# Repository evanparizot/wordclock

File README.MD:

# WordClock

This project is not a word clock based on the [wikipedia](https://en.wikipedia.org/wiki/Word_clock) definition, but rather just an aesthetic choice of representing time. Rather than showing something like a clock face or time in 12 hour / 24 hour format, a wordclock spells out the time using words. One of the more well known examples of wordclocks being produced is from the company [QLOCKTWO](https://qlocktwo.com/us?___from_store=de). Unfortunately, at it's retail price of $1,500+, they can be pretty expensive.

This project is to provide files for those who wish to build their own instead. It's been inspired by repositories such as [this](https://github.com/LikeClockwork/LargeWordClock) on providing both the pcb schematics, as well source code for anyone to look at. 

## Project Overview

Included in this repository are the graphics used to make up the clock face, the pcb schematics that outline the circuitry for the clock, as well the source code for the firmware used to run the wordclock. You can find each in their respective repostories. 

The pcb schematics were made using a mixture of Altium Designer and KiCad. The microcontroller is a variant of the STM32, with source code written in Rust. Each sub folder has further details on how to work with each of those components.

## Development Progress

Developmet of this project is ongoing and will be for some time. I will be keeping milestones in a Github project for the repository to track progress.

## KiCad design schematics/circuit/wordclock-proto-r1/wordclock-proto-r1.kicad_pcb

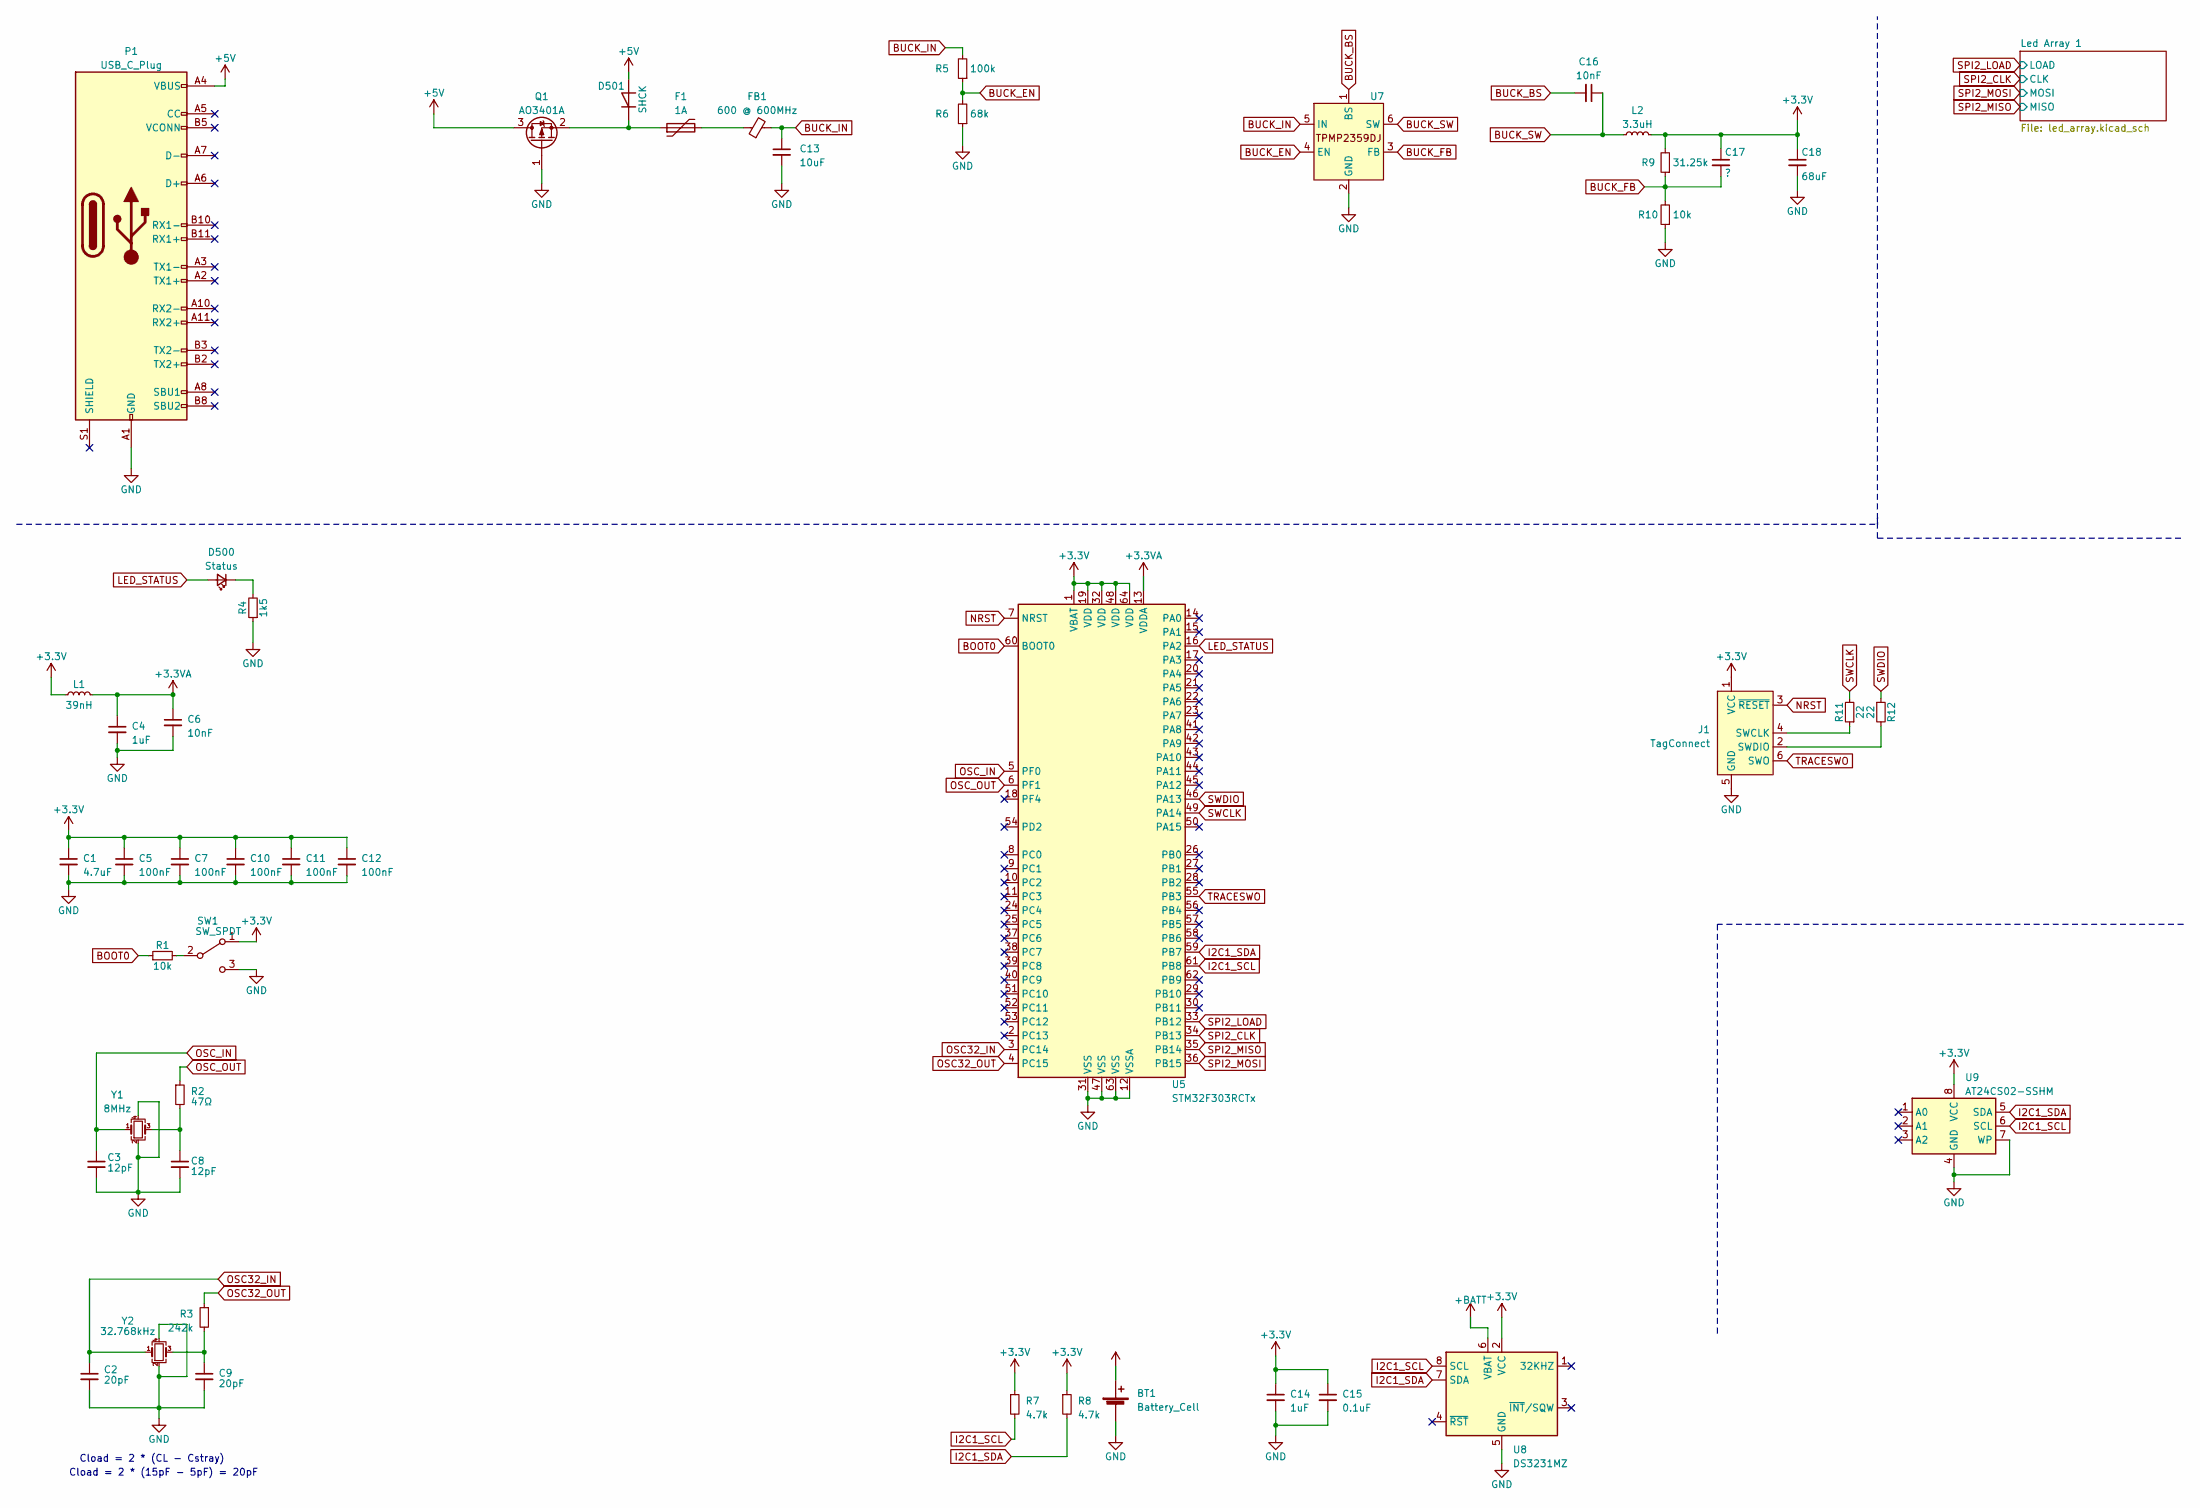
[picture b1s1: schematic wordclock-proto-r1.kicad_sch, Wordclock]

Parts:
BT1: Battery_Cell; BatteryHolder_Keystone_3002_1x2032
C1: 4.7uF; C_0603_1608Metric
C2, C9: 20pF; C_0402_1005Metric
C3, C8: 12pF; C_0402_1005Metric
C4, C14: 1uF; C_0402_1005Metric
C5, C7, C10, C11, C12: 100nF; C_0402_1005Metric
C6: 10nF; C_0402_1005Metric
C13: 10uF; C_0805_2012Metric
C15: 0.1uF; C_0402_1005Metric
C16: 10nF; C_0603_1608Metric
C17: ?; C_0603_1608Metric
C18: 68uF; C_0603_1608Metric
D500: Status; LED_0603_1608Metric
D501: SHCK; D_SOD-123
F1: 1A; Fuse_1206_3216Metric
FB1: 600 @ 600MHz; L_0805_2012Metric
J1: TagConnect; Tag-Connect_TC2030-IDC-FP_2x03_P1.27mm_Vertical
L1: 39nH; L_Sunlord_MWSA0518S
L2: 3.3uH; L_0402_1005Metric
P1: USB_C_Plug; USB_C_Receptacle_GCT_USB4115-03-C
Q1: AO3401A; SOT-23
R1: 10k; R_0603_1608Metric
R2: 47Ω; R_0402_1005Metric
R3: 242k; R_0402_1005Metric
R4: 1k5; R_0402_1005Metric
R5: 100k; R_0805_2012Metric
R6: 68k; R_0805_2012Metric
R7, R8: 4.7k; R_0402_1005Metric
R9: 31.25k; R_0805_2012Metric
R10: 10k; R_0805_2012Metric
R11, R12: 22; R_0603_1608Metric
SW1: SW_SPDT; SW_SPDT_PCM12
U5: STM32F303RCTx; LQFP-64_10x10mm_P0.5mm
U7: SOT-23-6
U8: DS3231MZ; SOIC-8_3.9x4.9mm_P1.27mm
U9: AT24CS02-SSHM; SOIC-8_3.9x4.9mm_P1.27mm
Y1: 8MHz; Crystal_SMD_3225-4Pin_3.2x2.5mm
Y2: 32.768kHz; Crystal_SMD_3225-4Pin_3.2x2.5mm

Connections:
+3.3V: C1.1, C5.1, C7.1, C10.1, C11.1, C12.1, C14.1, C15.1, C17.1, C18.1, J1.1 (VCC), L1.1, L2.2, R7.1, R8.1, R9.2, SW1.1 (A), U5.1 (VBAT), U5.19 (VDD), U5.32 (VDD), U5.48 (VDD), U5.64 (VDD), U8.2 (VCC), U9.8 (VCC); also elsewhere on the board
+3.3VA: C4.1, C6.1, L1.2, U5.13 (VDDA)
+5V: D501.2 (A), P1.A4 (VBUS), P1.A9 (VBUS), P1.B4 (VBUS), P1.B9 (VBUS), Q1.3 (D)
+BATT: BT1.1 (+), U8.6 (VBAT)
BOOT0: R1.1, U5.60 (BOOT0)
BUCK_BS: C16.2, U7.1 (BS)
BUCK_EN: R5.1, R6.2, U7.4 (EN)
BUCK_FB: C17.2, R9.1, R10.2, U7.3 (FB)
BUCK_IN: C13.1, FB1.2, R5.2, U7.5 (IN)
BUCK_SW: C16.1, L2.1, U7.6 (SW)
GND: BT1.2 (-), C1.2, C2.2, C3.2, C4.2, C5.2, C6.2, C7.2, C8.2, C9.2, C10.2, C11.2, C12.2, C13.2, C14.2, C15.2, C18.2, J1.5 (GND), P1.A1 (GND), P1.A12 (GND), P1.B1 (GND), P1.B12 (GND), Q1.1 (G), R4.1, R6.1, R10.1, SW1.3 (C), U5.12 (VSSA), U5.31 (VSS), U5.47 (VSS), U5.63 (VSS), U7.2 (GND), U8.5 (GND), U9.4 (GND), U9.7 (WP), Y1.2, Y1.4, Y2.2, Y2.4; also elsewhere on the board
I2C1_SCL: R7.2, U5.61 (PB8), U8.8 (SCL), U9.6 (SCL)
I2C1_SDA: R8.2, U5.59 (PB7), U8.7 (SDA), U9.5 (SDA)
LED_STATUS: D500.2 (A), U5.16 (PA2)
NRST: J1.3 (~RESET), U5.7 (NRST)
unnamed: C8.1, R2.2, Y1.3
unnamed: C9.1, R3.2, Y2.3
unnamed: D500.1 (K), R4.2
unnamed: D501.1 (K), F1.1, Q1.2 (S)
unnamed: F1.2, FB1.1
unnamed: J1.4 (SWCLK), R11.1
unnamed: J1.2 (SWDIO), R12.2
unnamed: R1.2, SW1.2 (B)
OSC32_IN: C2.1, U5.3 (PC14), Y2.1
OSC32_OUT: R3.1, U5.4 (PC15)
OSC_IN: C3.1, U5.5 (PF0), Y1.1
OSC_OUT: R2.1, U5.6 (PF1)
SPI2_CLK: U5.34 (PB13); also elsewhere on the board
SPI2_LOAD: U5.33 (PB12); also elsewhere on the board
SPI2_MISO: U5.35 (PB14); also elsewhere on the board
SPI2_MOSI: U5.36 (PB15); also elsewhere on the board
SWCLK: R11.2, U5.49 (PA14)
SWDIO: R12.1, U5.46 (PA13)
TRACESWO: J1.6 (SWO), U5.55 (PB3)

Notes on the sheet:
Cload = 2 * (15pF - 5pF) = 20pF
Cload = 2 * (CL - Cstray)

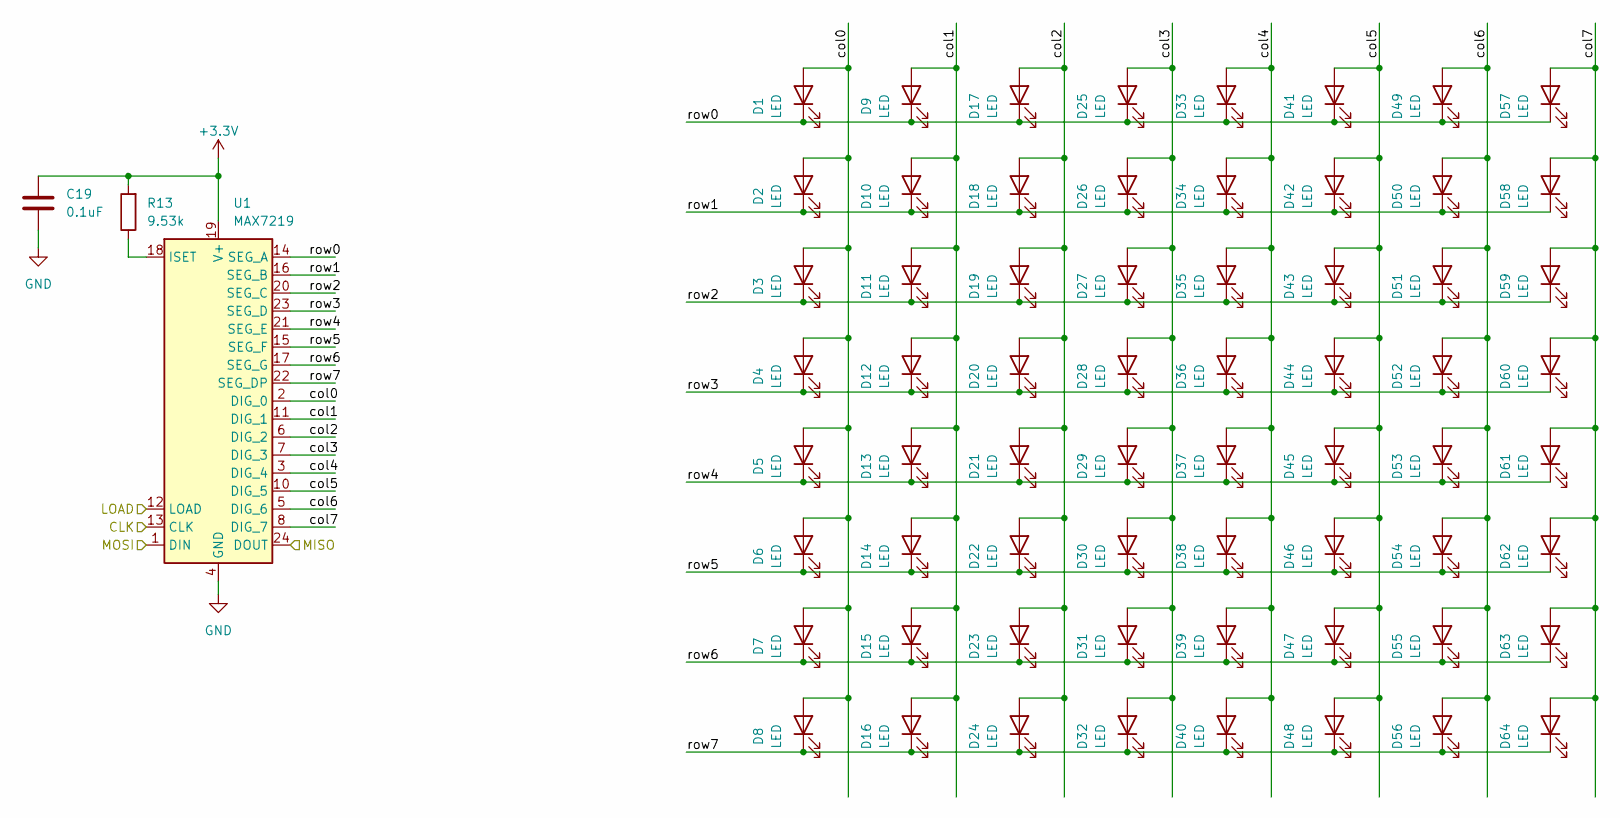
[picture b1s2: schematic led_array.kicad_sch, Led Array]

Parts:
C19: 0.1uF; C_0805_2012Metric
D1, D2, D3, D4, D5, D6, D7, D8, D9, D10, D11, D12, D13, D14, D15, D16, D17, D18, D19, D20, D21, D22, D23, D24, D25, D26, D27, D28, D29, D30, D31, D32, D33, D34, D35, D36, D37, D38, D39, D40, D41, D42, D43, D44, D45, D46, D47, D48, D49, D50, D51, D52, D53, D54, D55, D56, D57, D58, D59, D60, D61, D62, D63, D64: LED; LED_2010_5025Metric_Pad1.52x2.65mm_HandSolder
R13: 9.53k; R_0805_2012Metric
U1: MAX7219; SOIC-24W_7.5x15.4mm_P1.27mm

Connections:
+3.3V: C19.1, R13.2, U1.19 (V+); also elsewhere on the board
/Led Array 1/col0: D1.2 (A), D2.2 (A), D3.2 (A), D4.2 (A), D5.2 (A), D6.2 (A), D7.2 (A), D8.2 (A), U1.2 (DIG_0)
/Led Array 1/col1: D9.2 (A), D10.2 (A), D11.2 (A), D12.2 (A), D13.2 (A), D14.2 (A), D15.2 (A), D16.2 (A), U1.11 (DIG_1)
/Led Array 1/col2: D17.2 (A), D18.2 (A), D19.2 (A), D20.2 (A), D21.2 (A), D22.2 (A), D23.2 (A), D24.2 (A), U1.6 (DIG_2)
/Led Array 1/col3: D25.2 (A), D26.2 (A), D27.2 (A), D28.2 (A), D29.2 (A), D30.2 (A), D31.2 (A), D32.2 (A), U1.7 (DIG_3)
/Led Array 1/col4: D33.2 (A), D34.2 (A), D35.2 (A), D36.2 (A), D37.2 (A), D38.2 (A), D39.2 (A), D40.2 (A), U1.3 (DIG_4)
/Led Array 1/col5: D41.2 (A), D42.2 (A), D43.2 (A), D44.2 (A), D45.2 (A), D46.2 (A), D47.2 (A), D48.2 (A), U1.10 (DIG_5)
/Led Array 1/col6: D49.2 (A), D50.2 (A), D51.2 (A), D52.2 (A), D53.2 (A), D54.2 (A), D55.2 (A), D56.2 (A), U1.5 (DIG_6)
/Led Array 1/col7: D57.2 (A), D58.2 (A), D59.2 (A), D60.2 (A), D61.2 (A), D62.2 (A), D63.2 (A), D64.2 (A), U1.8 (DIG_7)
/Led Array 1/row0: D1.1 (K), D9.1 (K), D17.1 (K), D25.1 (K), D33.1 (K), D41.1 (K), D49.1 (K), D57.1 (K), U1.14 (SEG_A)
/Led Array 1/row1: D2.1 (K), D10.1 (K), D18.1 (K), D26.1 (K), D34.1 (K), D42.1 (K), D50.1 (K), D58.1 (K), U1.16 (SEG_B)
/Led Array 1/row2: D3.1 (K), D11.1 (K), D19.1 (K), D27.1 (K), D35.1 (K), D43.1 (K), D51.1 (K), D59.1 (K), U1.20 (SEG_C)
/Led Array 1/row3: D4.1 (K), D12.1 (K), D20.1 (K), D28.1 (K), D36.1 (K), D44.1 (K), D52.1 (K), D60.1 (K), U1.23 (SEG_D)
/Led Array 1/row4: D5.1 (K), D13.1 (K), D21.1 (K), D29.1 (K), D37.1 (K), D45.1 (K), D53.1 (K), D61.1 (K), U1.21 (SEG_E)
/Led Array 1/row5: D6.1 (K), D14.1 (K), D22.1 (K), D30.1 (K), D38.1 (K), D46.1 (K), D54.1 (K), D62.1 (K), U1.15 (SEG_F)
/Led Array 1/row6: D7.1 (K), D15.1 (K), D23.1 (K), D31.1 (K), D39.1 (K), D47.1 (K), D55.1 (K), D63.1 (K), U1.17 (SEG_G)
/Led Array 1/row7: D8.1 (K), D16.1 (K), D24.1 (K), D32.1 (K), D40.1 (K), D48.1 (K), D56.1 (K), D64.1 (K), U1.22 (SEG_DP)
GND: C19.2, U1.4 (GND), U1.9 (GND); also elsewhere on the board
unnamed: R13.1, U1.18 (ISET)
SPI2_CLK: U1.13 (CLK); also elsewhere on the board
SPI2_LOAD: U1.12 (LOAD); also elsewhere on the board
SPI2_MISO: U1.24 (DOUT); also elsewhere on the board
SPI2_MOSI: U1.1 (DIN); also elsewhere on the board

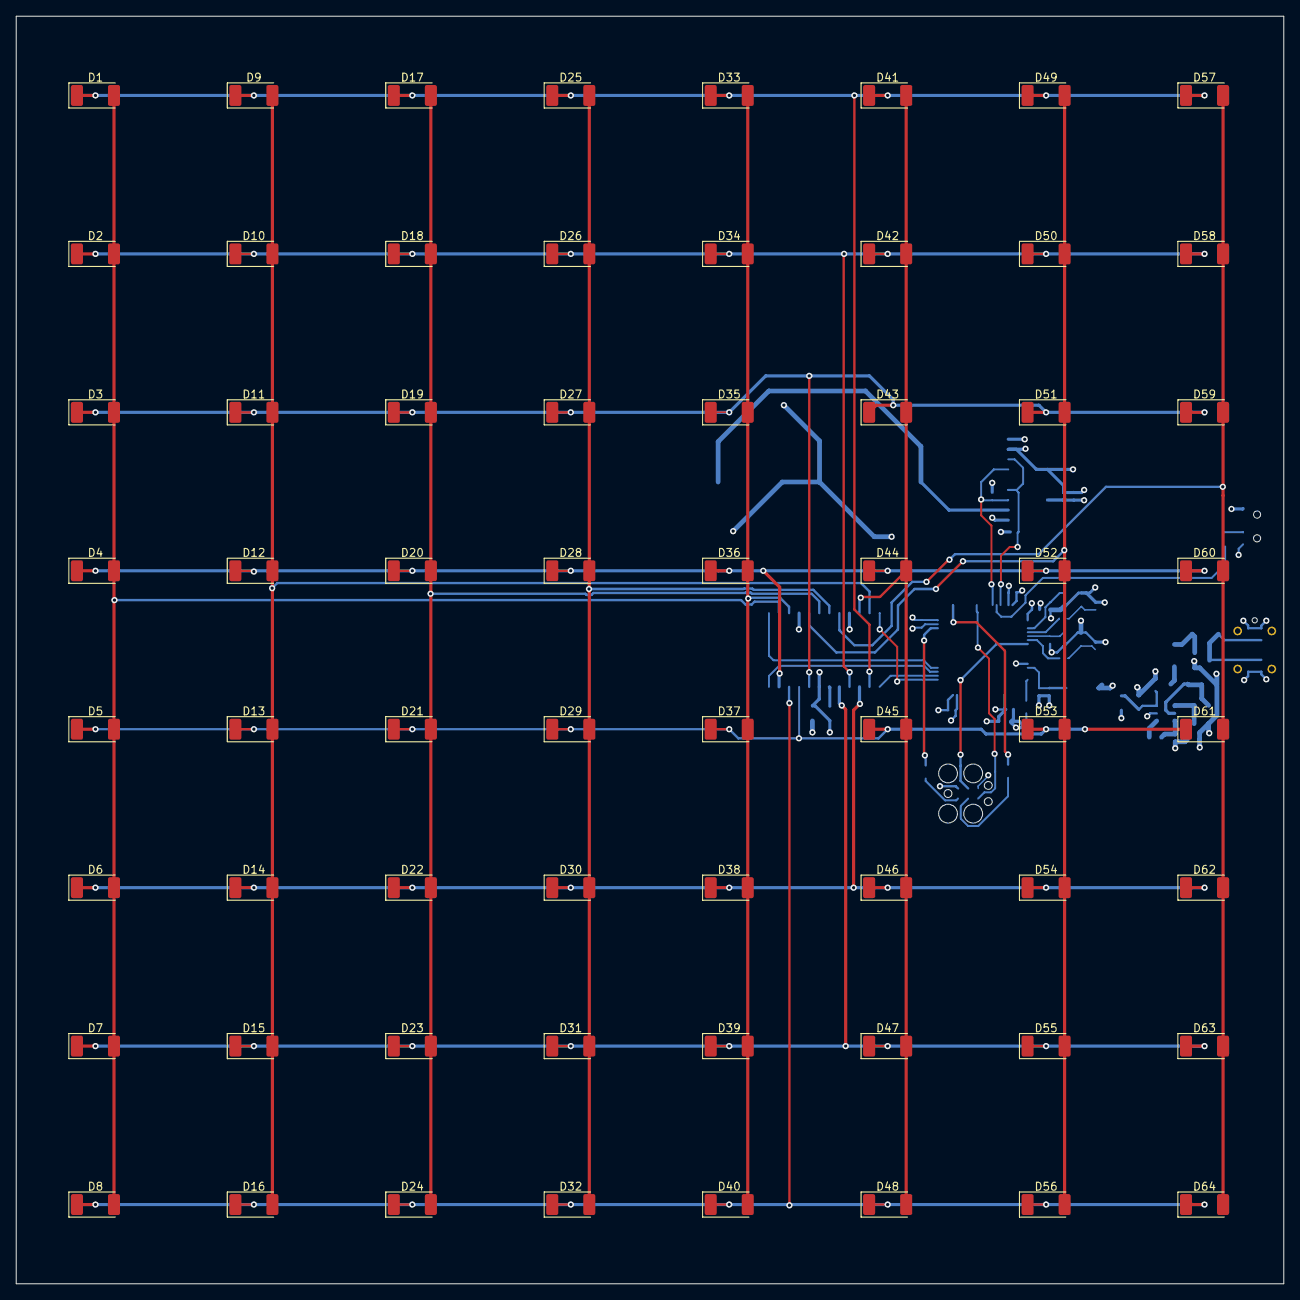
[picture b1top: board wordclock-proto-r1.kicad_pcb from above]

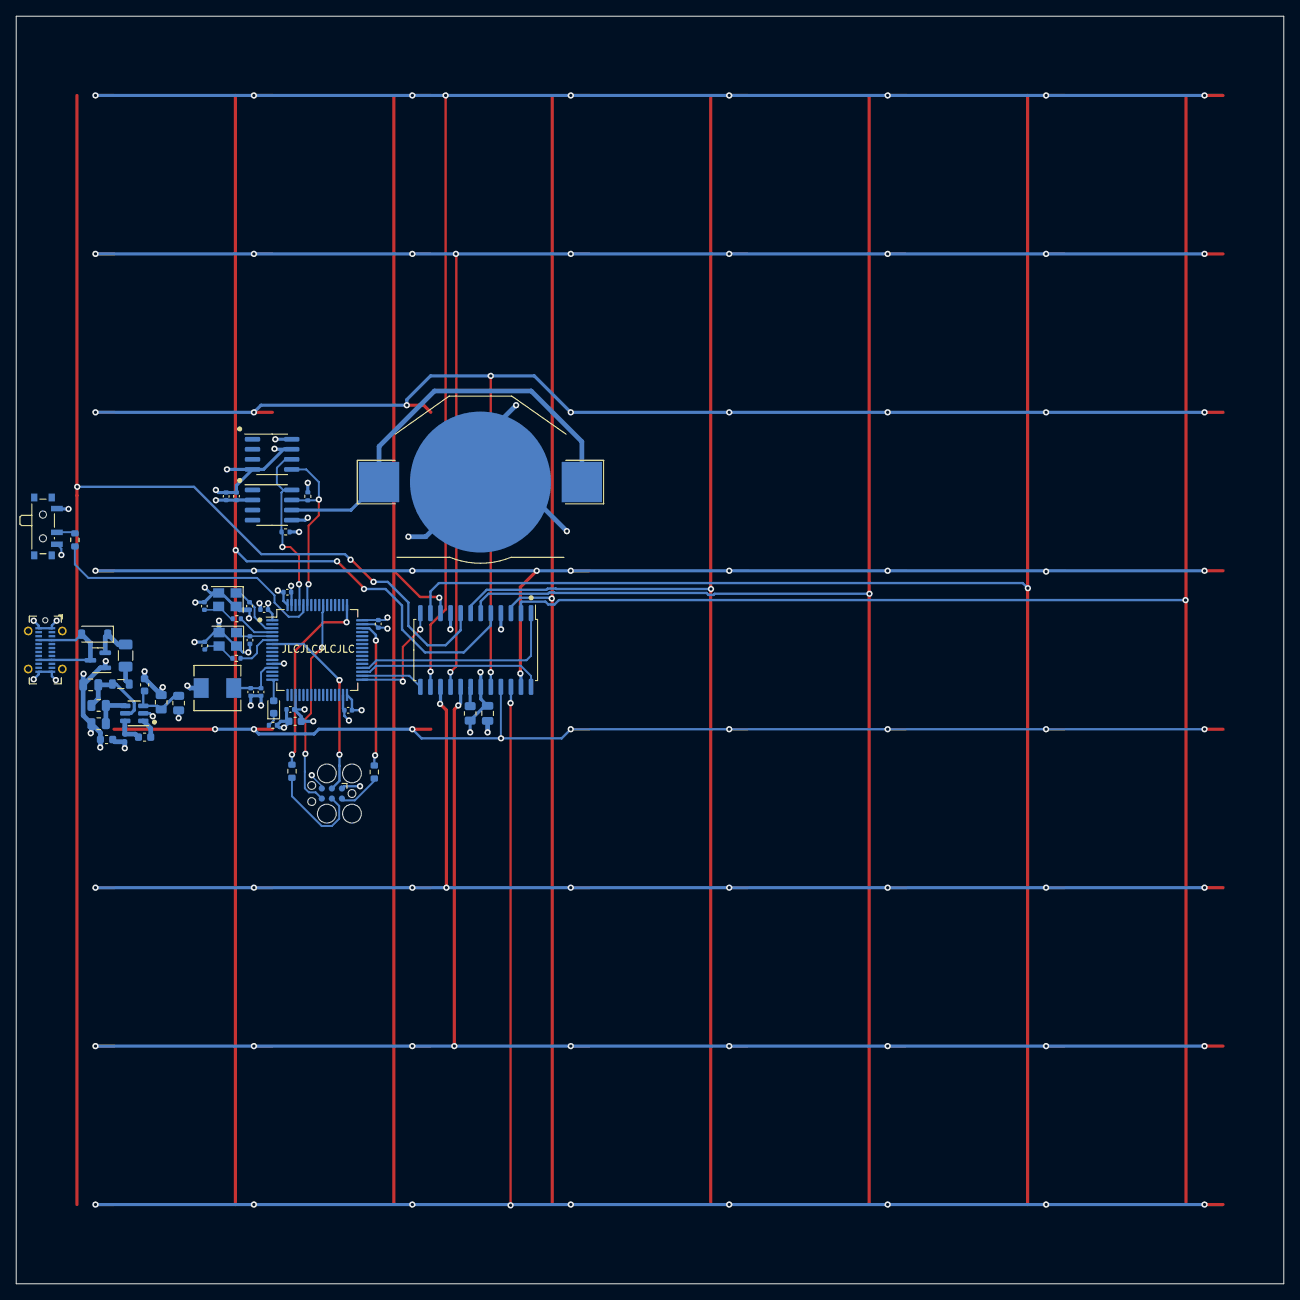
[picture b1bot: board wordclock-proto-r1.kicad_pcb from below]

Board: 4 copper layers, 160.0 x 160.0 mm, 114 parts (50 on the bottom side), 51 nets.

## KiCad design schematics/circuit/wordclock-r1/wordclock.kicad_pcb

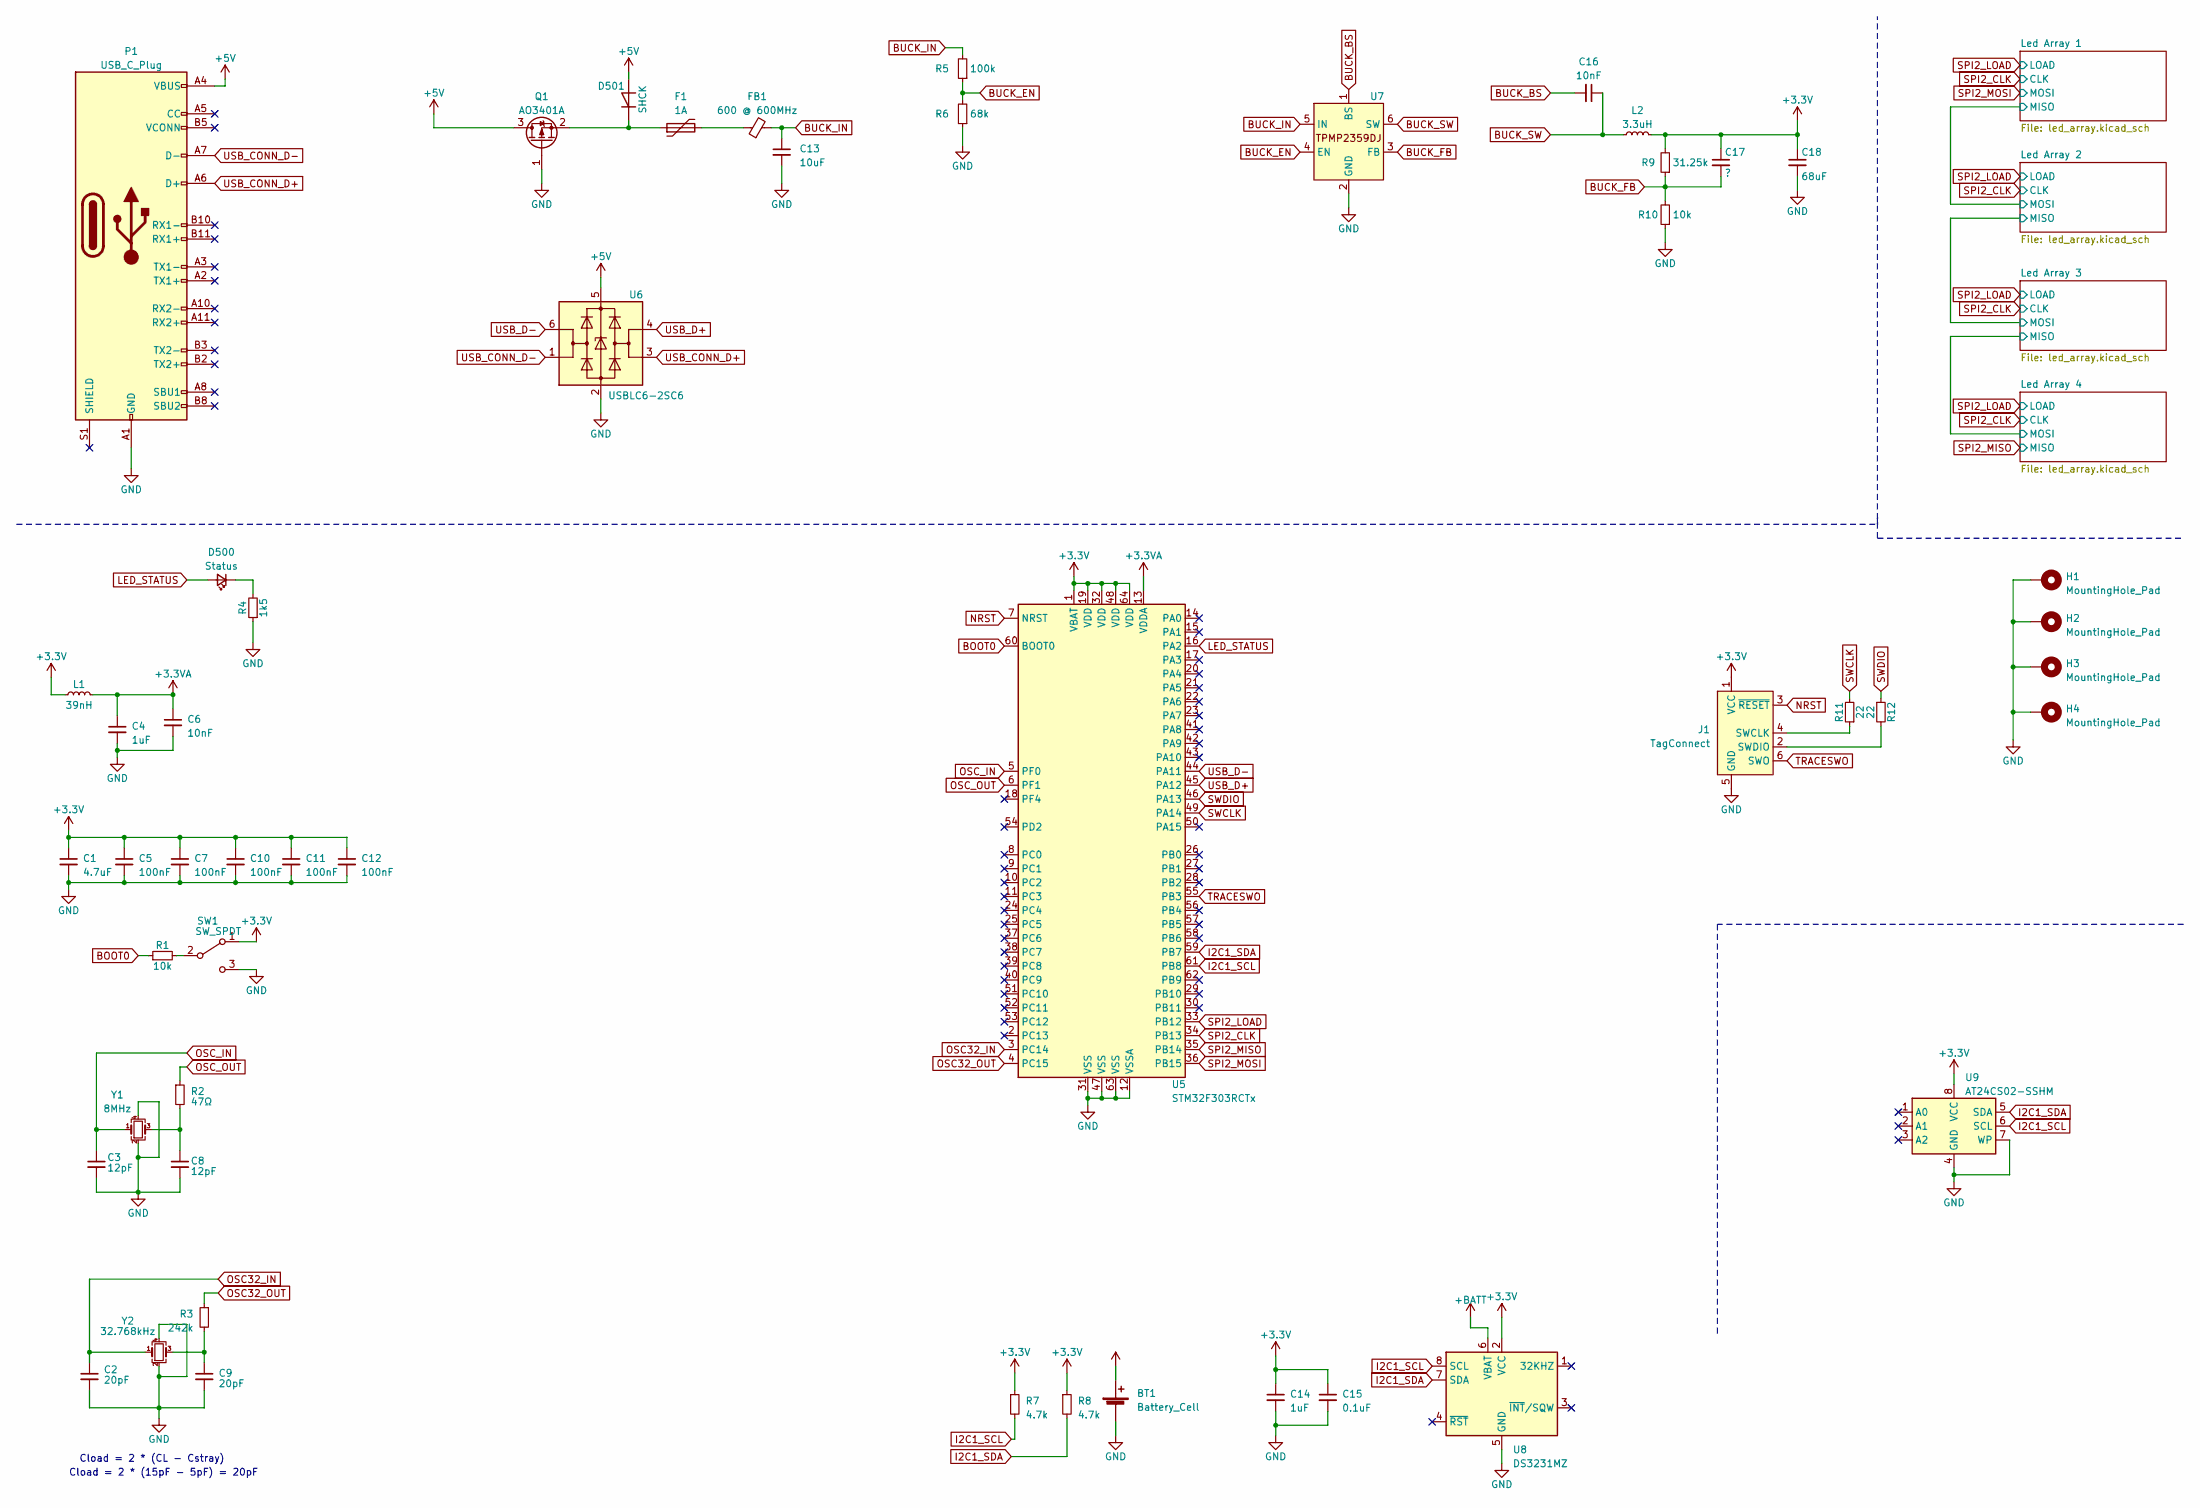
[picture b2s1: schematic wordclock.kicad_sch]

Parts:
BT1: Battery_Cell; BatteryHolder_Keystone_3002_1x2032
C1: 4.7uF; C_0603_1608Metric
C2, C9: 20pF; C_0402_1005Metric
C3, C8: 12pF; C_0402_1005Metric
C4, C14: 1uF; C_0402_1005Metric
C5, C7, C10, C11, C12: 100nF; C_0402_1005Metric
C6: 10nF; C_0402_1005Metric
C13: 10uF; C_0805_2012Metric
C15: 0.1uF; C_0402_1005Metric
C16: 10nF; C_0603_1608Metric
C17: ?; C_0603_1608Metric
C18: 68uF; C_0603_1608Metric
D500: Status; LED_0603_1608Metric
D501: SHCK; D_SOD-123
F1: 1A; Fuse_1206_3216Metric
FB1: 600 @ 600MHz; L_0805_2012Metric
H1, H2, H3, H4: MountingHole_Pad; MountingHole_4.3mm_M4_Pad_Via
J1: TagConnect; Tag-Connect_TC2030-IDC-FP_2x03_P1.27mm_Vertical
L1: 39nH; L_Sunlord_MWSA0518S
L2: 3.3uH; L_0402_1005Metric
P1: USB_C_Plug; USB_C_Receptacle_GCT_USB4115-03-C
Q1: AO3401A; SOT-23
R1: 10k; R_0603_1608Metric
R2: 47Ω; R_0402_1005Metric
R3: 242k; R_0402_1005Metric
R4: 1k5; R_0402_1005Metric
R5: 100k; R_0805_2012Metric
R6: 68k; R_0805_2012Metric
R7, R8: 4.7k; R_0402_1005Metric
R9: 31.25k; R_0805_2012Metric
R10: 10k; R_0805_2012Metric
R11, R12: 22; R_0603_1608Metric
SW1: SW_SPDT; SW_SPDT_PCM12
U5: STM32F303RCTx; LQFP-64_10x10mm_P0.5mm
U6: USBLC6-2SC6; SOT-23-6
U7: SOT-23-6
U8: DS3231MZ; SOIC-8_3.9x4.9mm_P1.27mm
U9: AT24CS02-SSHM; SOIC-8_3.9x4.9mm_P1.27mm
Y1: 8MHz; Crystal_SMD_3225-4Pin_3.2x2.5mm
Y2: 32.768kHz; Crystal_SMD_3225-4Pin_3.2x2.5mm

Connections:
+3.3V: C1.1, C5.1, C7.1, C10.1, C11.1, C12.1, C14.1, C15.1, C17.1, C18.1, J1.1 (VCC), L1.1, L2.2, R7.1, R8.1, R9.2, SW1.1 (A), U5.1 (VBAT), U5.19 (VDD), U5.32 (VDD), U5.48 (VDD), U5.64 (VDD), U8.2 (VCC), U9.8 (VCC); also elsewhere on the board
+3.3VA: C4.1, C6.1, L1.2, U5.13 (VDDA)
+5V: D501.2 (A), P1.A4 (VBUS), P1.A9 (VBUS), P1.B4 (VBUS), P1.B9 (VBUS), Q1.3 (D), U6.5 (VBUS)
+BATT: BT1.1 (+), U8.6 (VBAT)
BOOT0: R1.1, U5.60 (BOOT0)
BUCK_BS: C16.2, U7.1 (BS)
BUCK_EN: R5.1, R6.2, U7.4 (EN)
BUCK_FB: C17.2, R9.1, R10.2, U7.3 (FB)
BUCK_IN: C13.1, FB1.2, R5.2, U7.5 (IN)
BUCK_SW: C16.1, L2.1, U7.6 (SW)
GND: BT1.2 (-), C1.2, C2.2, C3.2, C4.2, C5.2, C6.2, C7.2, C8.2, C9.2, C10.2, C11.2, C12.2, C13.2, C14.2, C15.2, C18.2, H1.1, H2.1, H3.1, H4.1, J1.5 (GND), P1.A1 (GND), P1.A12 (GND), P1.B1 (GND), P1.B12 (GND), Q1.1 (G), R4.1, R6.1, R10.1, SW1.3 (C), U5.12 (VSSA), U5.31 (VSS), U5.47 (VSS), U5.63 (VSS), U6.2 (GND), U7.2 (GND), U8.5 (GND), U9.4 (GND), U9.7 (WP), Y1.2, Y1.4, Y2.2, Y2.4; also elsewhere on the board
I2C1_SCL: R7.2, U5.61 (PB8), U8.8 (SCL), U9.6 (SCL)
I2C1_SDA: R8.2, U5.59 (PB7), U8.7 (SDA), U9.5 (SDA)
LED_STATUS: D500.2 (A), U5.16 (PA2)
NRST: J1.3 (~RESET), U5.7 (NRST)
unnamed: C8.1, R2.2, Y1.3
unnamed: C9.1, R3.2, Y2.3
unnamed: D500.1 (K), R4.2
unnamed: D501.1 (K), F1.1, Q1.2 (S)
unnamed: F1.2, FB1.1
unnamed: J1.4 (SWCLK), R11.1
unnamed: J1.2 (SWDIO), R12.2
unnamed: R1.2, SW1.2 (B)
OSC32_IN: C2.1, U5.3 (PC14), Y2.1
OSC32_OUT: R3.1, U5.4 (PC15)
OSC_IN: C3.1, U5.5 (PF0), Y1.1
OSC_OUT: R2.1, U5.6 (PF1)
SPI2_CLK: U5.34 (PB13); also elsewhere on the board
SPI2_LOAD: U5.33 (PB12); also elsewhere on the board
SPI2_MISO: U5.35 (PB14); also elsewhere on the board
SPI2_MOSI: U5.36 (PB15); also elsewhere on the board
SWCLK: R11.2, U5.49 (PA14)
SWDIO: R12.1, U5.46 (PA13)
TRACESWO: J1.6 (SWO), U5.55 (PB3)
USB_CONN_D+: P1.A6 (D+), U6.3 (I/O2)
USB_CONN_D-: P1.A7 (D-), U6.1 (I/O1)
USB_D+: U5.45 (PA12), U6.4 (I/O2)
USB_D-: U5.44 (PA11), U6.6 (I/O1)

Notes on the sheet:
Cload = 2 * (15pF - 5pF) = 20pF
Cload = 2 * (CL - Cstray)

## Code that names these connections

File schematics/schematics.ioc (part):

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Mcu.Name=STM32F303R(B-C)Tx
Mcu.Package=LQFP64
Mcu.UserName=STM32F303RCTx
PA11.Mode=Device
PA11.Signal=USB_DM
PA12.Mode=Device
PA12.Signal=USB_DP
PA13.Mode=Trace_Asynchronous_SW
PA13.Signal=SYS_JTMS-SWDIO
PA14.Mode=Trace_Asynchronous_SW
PA14.Signal=SYS_JTCK-SWCLK
PB13.Mode=Full_Duplex_Master
PB13.Signal=SPI2_SCK
PB14.Mode=Full_Duplex_Master
PB14.Signal=SPI2_MISO
PB15.Mode=Full_Duplex_Master
PB15.Signal=SPI2_MOSI
PB3.Mode=Trace_Asynchronous_SW
PB3.Signal=SYS_JTDO-TRACESWO
PC14-OSC32_IN.Mode=LSE-External-Oscillator
PC14-OSC32_IN.Signal=RCC_OSC32_IN
PC15-OSC32_OUT.Mode=LSE-External-Oscillator
PC15-OSC32_OUT.Signal=RCC_OSC32_OUT
PF0-OSC_IN.Mode=HSE-External-Oscillator
PF0-OSC_IN.Signal=RCC_OSC_IN
PF1-OSC_OUT.Mode=HSE-External-Oscillator
PF1-OSC_OUT.Signal=RCC_OSC_OUT
RCC.HSEPLLFreq_Value=8000000
RCC.HSE_VALUE=8000000
RCC.SYSCLKFreq_VALUE=8000000
board=custom

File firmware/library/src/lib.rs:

#![no_std]
extern crate alloc;

use alloc_cortex_m::CortexMHeap;

#[global_allocator]
static ALLOCATOR: CortexMHeap = CortexMHeap::empty();

use alloc::boxed::Box;
use ds323x::Ds323x;
use max7219::MAX7219;
pub use panic_itm; // panic handler

pub use cortex_m::{asm::bkpt, iprint, iprintln, peripheral::ITM};
pub use cortex_m_rt::entry;

use stm32f3xx_hal::i2c::I2c;
pub use stm32f3xx_hal::{
    delay::Delay,
    gpio::{gpioe, Output, PushPull},
    hal::blocking::delay::DelayMs,
    pac,
    prelude::*,
    spi::Spi,
};

pub mod clock;
use clock::*;
use time::times::TimeMode;

pub mod time;

const HEAP_SIZE: usize = 1024;

pub fn init(mode: Box<dyn TimeMode>) -> Clock {
    unsafe { ALLOCATOR.init(cortex_m_rt::heap_start() as usize, HEAP_SIZE) }

    let cp = cortex_m::Peripherals::take().unwrap();
    let dp = pac::Peripherals::take().unwrap();

    let mut flash = dp.FLASH.constrain();
    let mut rcc = dp.RCC.constrain();

    let mut gpiob = dp.GPIOB.split(&mut rcc.ahb);

    let clocks = rcc
        .cfgr
        .sysclk(64.MHz())
        .pclk1(32.MHz())
        .pclk2(32.MHz())
        .freeze(&mut flash.acr);

    let delay = Delay::new(cp.SYST, clocks);

    //  /$$$$$$  /$$$$$$   /$$$$$$
    // |_  $$_/ /$$__  $$ /$$__  $$
    //   | $$  |__/  \ $$| $$  \__/
    //   | $$    /$$$$$$/| $$
    //   | $$   /$$____/ | $$
    //   | $$  | $$      | $$    $$
    //  /$$$$$$| $$$$$$$$|  $$$$$$/
    // |______/|________/ \______/
    //
    // DS3231
    // Default time is 01/01/00T00:00:00
    // https://github.com/eldruin/driver-examples/blob/master/stm32f3-discovery/examples/ds3231-f3.rs

    let mut scl =
        gpiob
            .pb6
            .into_af_open_drain(&mut gpiob.moder, &mut gpiob.otyper, &mut gpiob.afrl);
    let mut sda =
        gpiob
            .pb7
            .into_af_open_drain(&mut gpiob.moder, &mut gpiob.otyper, &mut gpiob.afrl);

    scl.internal_pull_up(&mut gpiob.pupdr, true);
    sda.internal_pull_up(&mut gpiob.pupdr, true);

    let i2c = I2c::new(dp.I2C1, (scl, sda), 100_000.Hz(), clocks, &mut rcc.apb1);
    let rtc = Ds323x::new_ds3231(i2c);

    //   /$$$$$$  /$$$$$$$  /$$$$$$
    //  /$$__  $$| $$__  $$|_  $$_/
    // | $$  \__/| $$  \ $$  | $$
    // |  $$$$$$ | $$$$$$$/  | $$
    //  \____  $$| $$____/   | $$
    //  /$$  \ $$| $$        | $$
    // |  $$$$$$/| $$       /$$$$$$
    //  \______/ |__/      |______/
    //
    // https://github.com/stm32-rs/stm32f3xx-hal/blob/master/examples/spi.rs
    // https://github.com/almindor/max7219-examples/blob/master/examples/display_spi.rs
    // https://github.com/almindor/max7219

    let cs = gpiob
        .pb12
        .into_push_pull_output(&mut gpiob.moder, &mut gpiob.otyper);
    let sck = gpiob
        .pb13
        .into_af_push_pull(&mut gpiob.moder, &mut gpiob.otyper, &mut gpiob.afrh);
    let miso = gpiob
        .pb14
        .into_af_push_pull(&mut gpiob.moder, &mut gpiob.otyper, &mut gpiob.afrh);
    let mosi = gpiob
        .pb15
        .into_af_push_pull(&mut gpiob.moder, &mut gpiob.otyper, &mut gpiob.afrh);

    let spi = Spi::new(dp.SPI2, (sck, miso, mosi), 3.MHz(), clocks, &mut rcc.apb1);

    let displays = 4;
    let mut display = MAX7219::from_spi_cs(displays, spi, cs).unwrap();

    display.power_on().unwrap();
    for a in 0..displays {
        display.clear_display(a).unwrap();
        display.set_intensity(a, 8).unwrap();
    }

    Clock {
        display: display,
        clock: rtc,
        delay: delay,
        mode: mode,
    }
}
